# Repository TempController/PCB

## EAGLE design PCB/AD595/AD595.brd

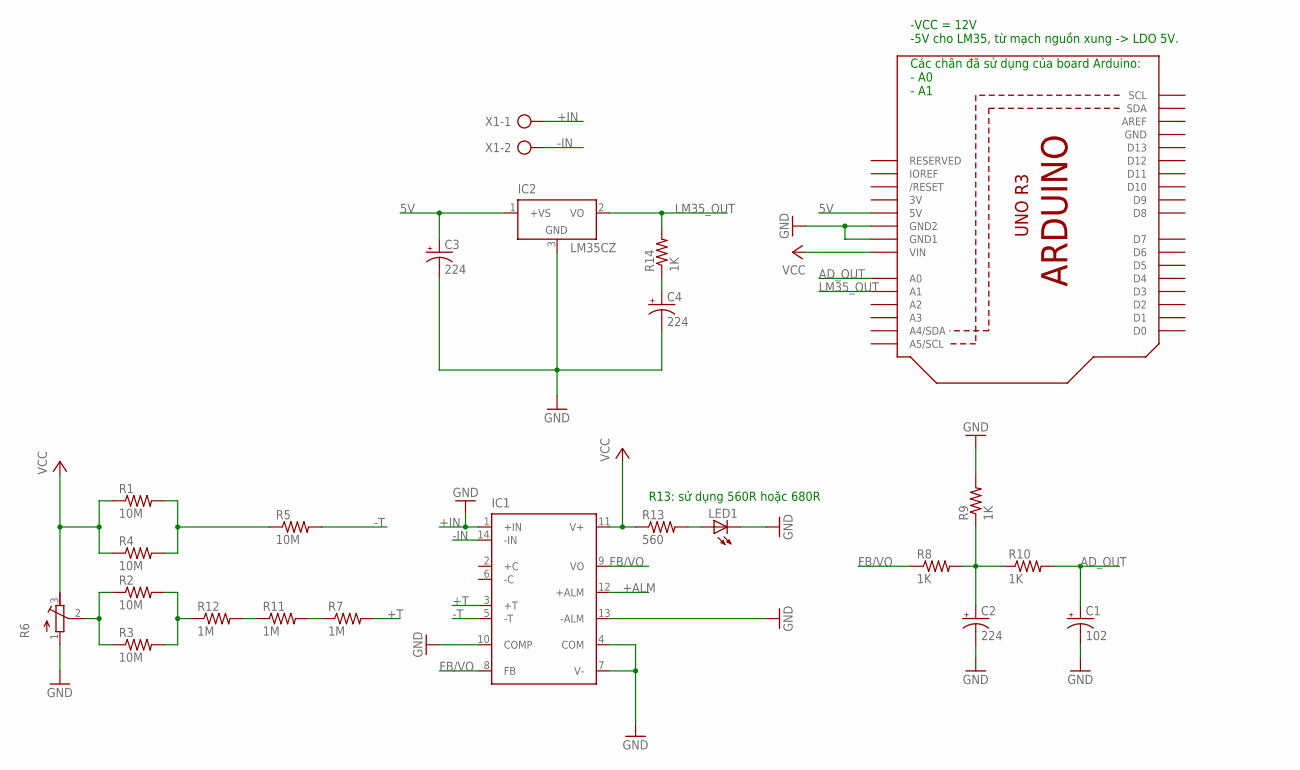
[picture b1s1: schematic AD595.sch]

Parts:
C1: 102; E2,5-6
C2, C3, C4: 224; E2,5-6
IC1: AD595; DIL14
IC2: LM35CZ; TO92
LED1: LED3MM
R1, R2, R3, R4, R5: 10M; 0207/10
R6: R-TRIMM64W; RTRIM64W
R7, R11, R12: 1M; 0207/10
R8, R9, R10, R14: 1K; 0207/10
R13: 560; 0207/10
U1: ARDUINOR3-DIMENSION; ARDUINOR3
X1: AK500/2-H

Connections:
3V: U1.3V
5V: C3.+, IC2.1 (+VS), U1.5V
+ALM: IC1.12 (+ALM)
+IN: IC1.1 (+IN), X1.1
+T: IC1.3 (+T), R7.2
-IN: IC1.14 (-IN), X1.2
-T: IC1.5 (-T), R5.2
AD_OUT: C1.+, R10.2, U1.A0
FB/VO: IC1.8 (FB), IC1.9 (VO), R8.1
GND: C1.-, C2.-, C3.-, C4.-, IC1.4 (COM), IC1.7 (V-), IC1.10 (COMP), IC1.13 (-ALM), IC2.3 (GND), LED1.K (C), R6.1 (E), R9.2, U1.GND, U1.GND1, U1.GND2
LM35_OUT: IC2.2 (VO), R14.2, U1.A1
unnamed: LED1.A, R13.2
unnamed: R1.2, R4.2, R5.1
unnamed: R2.1, R3.1, R6.2 (S)
unnamed: R11.1, R12.2
unnamed: R2.2, R3.2, R12.1
unnamed: R7.1, R11.2
unnamed: C4.+, R14.1
unnamed: C2.+, R8.2, R9.1, R10.1
VCC: IC1.11 (V+), R1.1, R4.1, R6.3 (A), R13.1, U1.VIN

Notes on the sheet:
-VCC = 12V -5V cho LM35, từ mạch nguồn xung -> LDO 5V.
R13: sử dụng 560R hoặc 680R
Các chân đã sử dụng của board Arduino: - A0 - A1

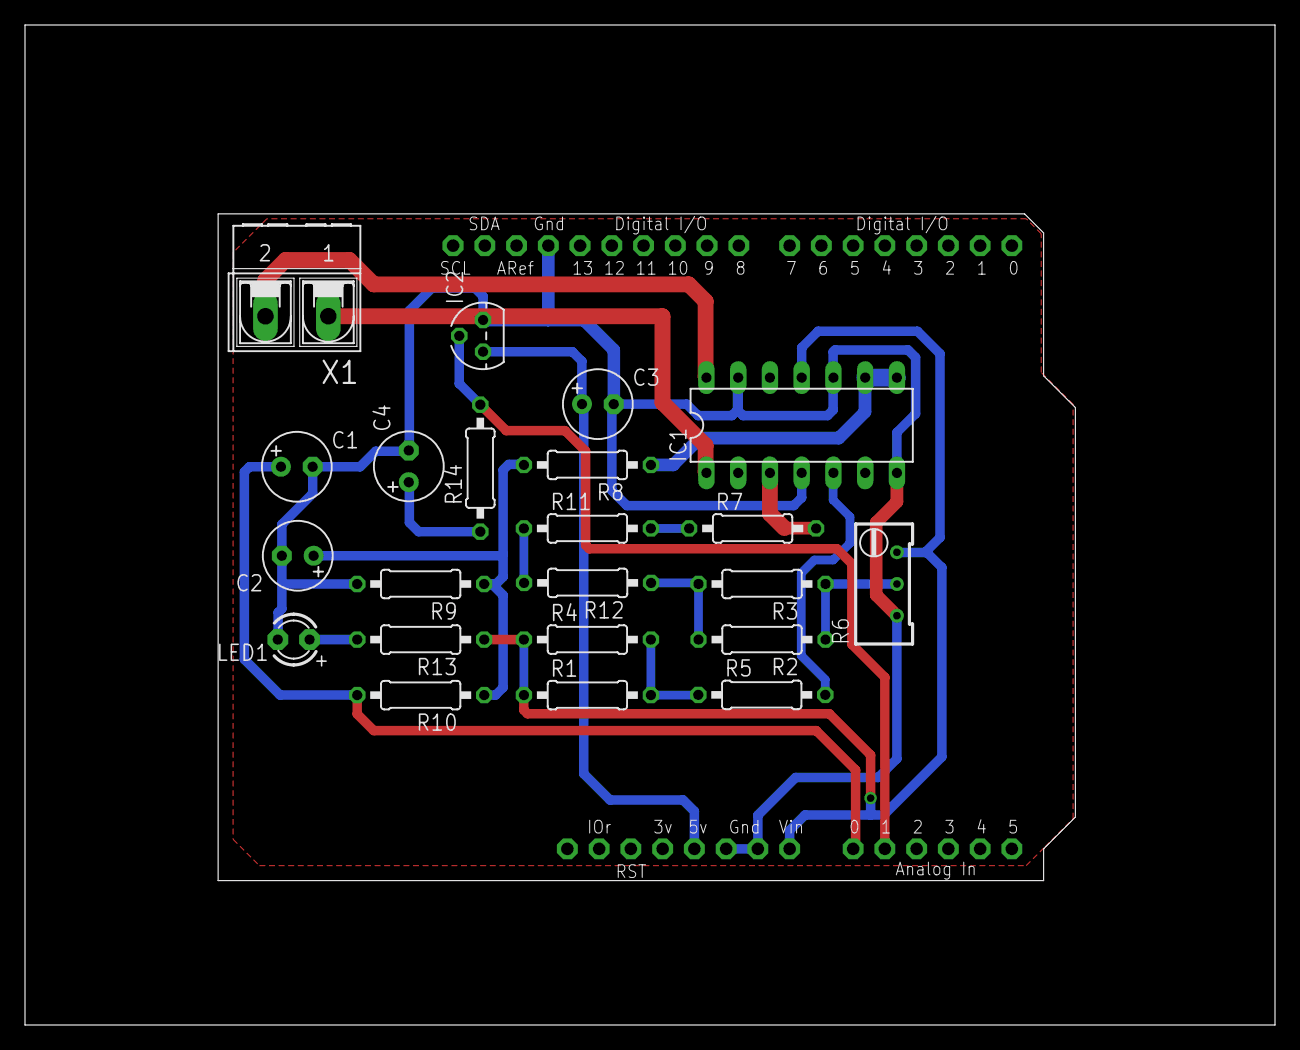
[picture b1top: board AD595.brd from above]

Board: 2 copper layers, 100.0 x 80.0 mm, 23 parts (0 on the bottom side), 18 nets.

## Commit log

2015-07-25 add board AD595
